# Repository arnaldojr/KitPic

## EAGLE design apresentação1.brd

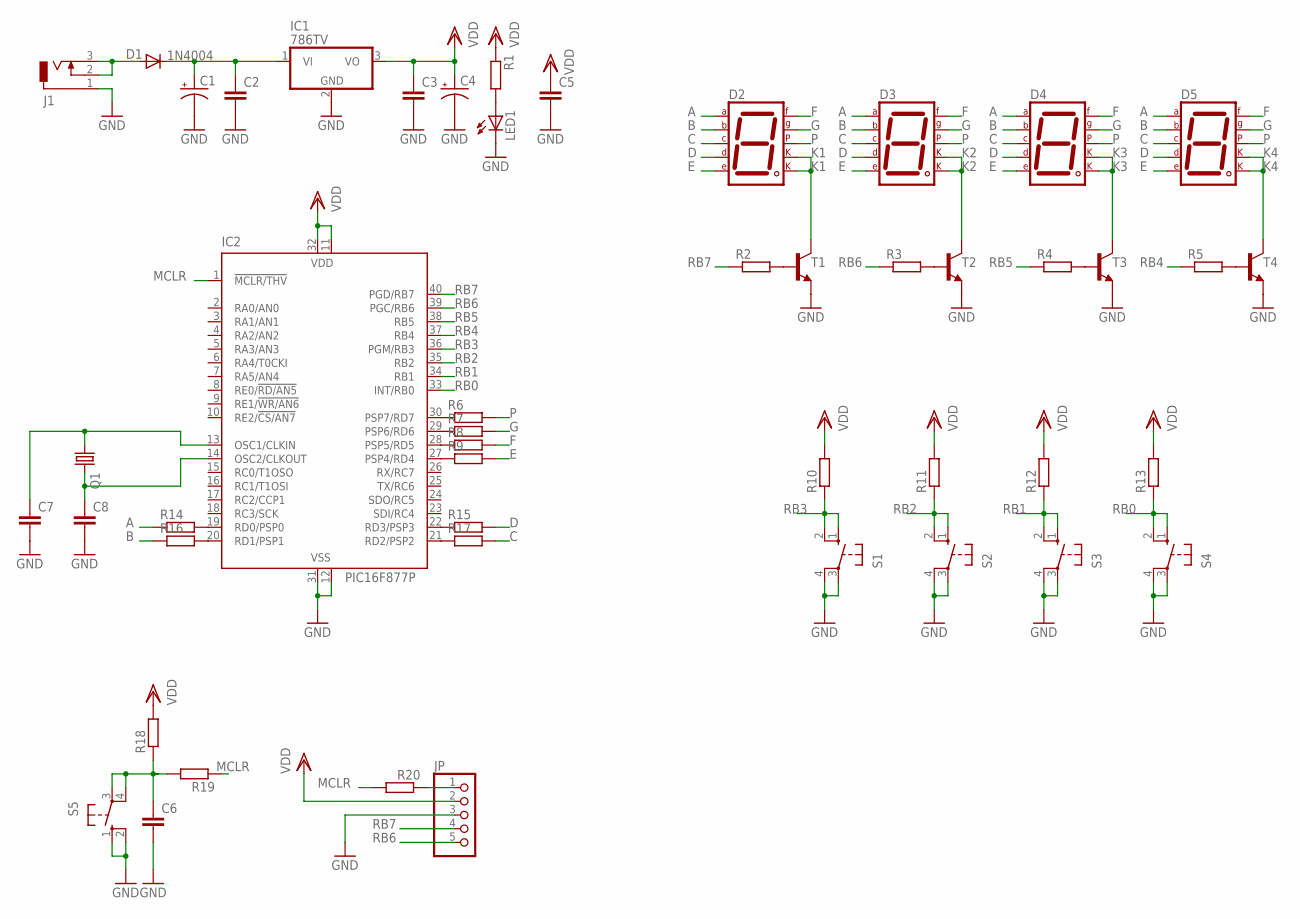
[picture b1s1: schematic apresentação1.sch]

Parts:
C1, C4: CPOL-USE2.5-5; E2,5-5
C2, C3, C5, C6, C7, C8: C-EU025-025X050; C025-025X050
D1: 1N4004; DO41-10
D2, D3, D4, D5: 7SEG-CK; 7SEG-13
IC1: 786TV; TO220V
IC2: PIC16F877P; DIL40
J1: DCJ0303
JP: PINHD-1X5; 1X05
LED1: LED5MM
Q1: CRYSTALHC49S; HC49/S
R1, R2, R3, R4, R5, R6, R7, R8, R9, R10, R11, R12, R13, R14, R15, R16, R17, R18, R19, R20: R-EU_0204/7; 0204/7
S1, S2, S3, S4: 10-XX; B3F-10XX
S5: 10-XX; B3F-10XX; MPN B3F-1000
T1, T2, T3, T4: BC337-16-NPN-TO92-CBE; TO92-CBE

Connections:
+VCC: D1.A, J1.2, J1.3
A: D2.7 (A), D3.7 (A), D4.7 (A), D5.7 (A), R14.1
B: D2.6 (B), D3.6 (B), D4.6 (B), D5.6 (B), R16.1
C: D2.4 (C), D3.4 (C), D4.4 (C), D5.4 (C), R17.2
D: D2.2 (D), D3.2 (D), D4.2 (D), D5.2 (D), R15.2
E: D2.1 (E), D3.1 (E), D4.1 (E), D5.1 (E), R9.2
F: D2.9 (F), D3.9 (F), D4.9 (F), D5.9 (F), R8.2
G: D2.10 (G), D3.10 (G), D4.10 (G), D5.10 (G), R7.2
GND: C1.-, C2.2, C3.2, C4.-, C5.2, C6.2, C7.2, C8.2, IC1.2 (GND), IC2.12 (VSS), IC2.31 (VSS), J1.1, JP.3, LED1.K (C), S1.3, S1.4 (P1), S2.3, S2.4 (P1), S3.3, S3.4 (P1), S4.3, S4.4 (P1), S5.1 (S), S5.2 (S1), T1.E, T2.E, T3.E, T4.E
K1: D2.3 (CK1), D2.8 (CK2), T1.C
K2: D3.3 (CK1), D3.8 (CK2), T2.C
K3: D4.3 (CK1), D4.8 (CK2), T3.C
K4: D5.3 (CK1), D5.8 (CK2), T4.C
MCLR: IC2.1 (!MCLR/THV), R19.1, R20.2
unnamed: C7.1, IC2.13 (OSC1/CLKIN), Q1.1
unnamed: C1.+, C2.1, D1.C, IC1.1 (VI)
unnamed: LED1.A, R1.2
unnamed: R2.2, T1.B
unnamed: R3.2, T2.B
unnamed: R4.2, T3.B
unnamed: R5.2, T4.B
unnamed: C6.1, R18.1, R19.2, S5.3, S5.4 (P1)
unnamed: IC2.30 (PSP7/RD7), R6.1
unnamed: IC2.29 (PSP6/RD6), R7.1
unnamed: IC2.28 (PSP5/RD5), R8.1
unnamed: IC2.27 (PSP4/RD4), R9.1
unnamed: IC2.22 (RD3/PSP3), R15.1
unnamed: IC2.21 (RD2/PSP2), R17.1
unnamed: IC2.20 (RD1/PSP1), R16.2
unnamed: IC2.19 (RD0/PSP0), R14.2
unnamed: C8.1, IC2.14 (OSC2/CLKOUT), Q1.2
unnamed: JP.1, R20.1
P: D2.5 (DP), D3.5 (DP), D4.5 (DP), D5.5 (DP), R6.2
RB0: IC2.33 (INT/RB0), R13.1, S4.1 (S), S4.2 (S1)
RB1: IC2.34 (RB1), R12.1, S3.1 (S), S3.2 (S1)
RB2: IC2.35 (RB2), R11.1, S2.1 (S), S2.2 (S1)
RB3: IC2.36 (PGM/RB3), R10.1, S1.1 (S), S1.2 (S1)
RB4: IC2.37 (RB4), R5.1
RB5: IC2.38 (RB5), R4.1
RB6: IC2.39 (PGC/RB6), JP.5, R3.1
RB7: IC2.40 (PGD/RB7), JP.4, R2.1
VDD: C3.1, C4.+, C5.1, IC1.3 (VO), IC2.11 (VDD), IC2.32 (VDD), JP.2, R1.1, R10.2, R11.2, R12.2, R13.2, R18.2

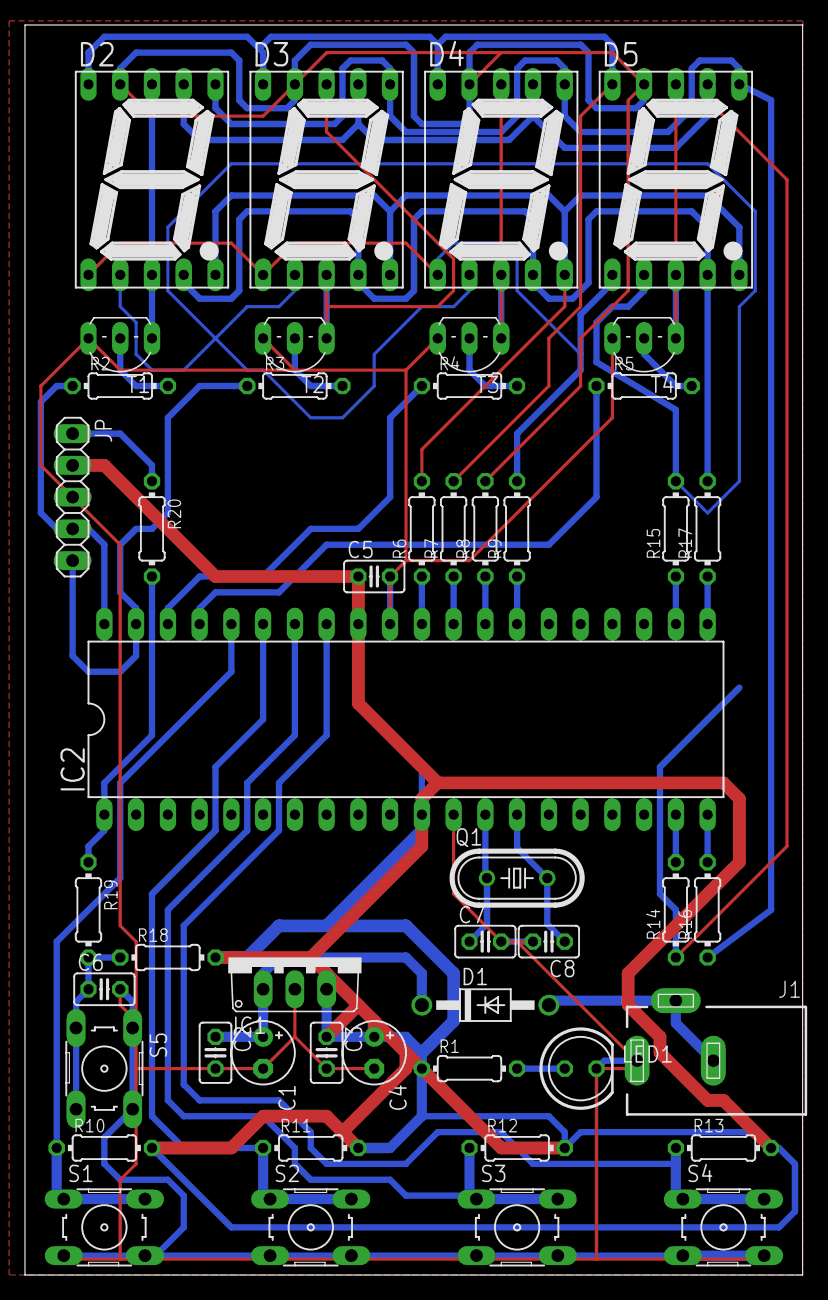
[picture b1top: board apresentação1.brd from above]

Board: 2 copper layers, 62.2 x 100.0 mm, 48 parts (0 on the bottom side), 42 nets.

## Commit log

2018-11-02 init commit
